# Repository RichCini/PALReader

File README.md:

This is a small archive of PAL reading code and schematics from Chuck Guzis as discussed on the VCF Forums.

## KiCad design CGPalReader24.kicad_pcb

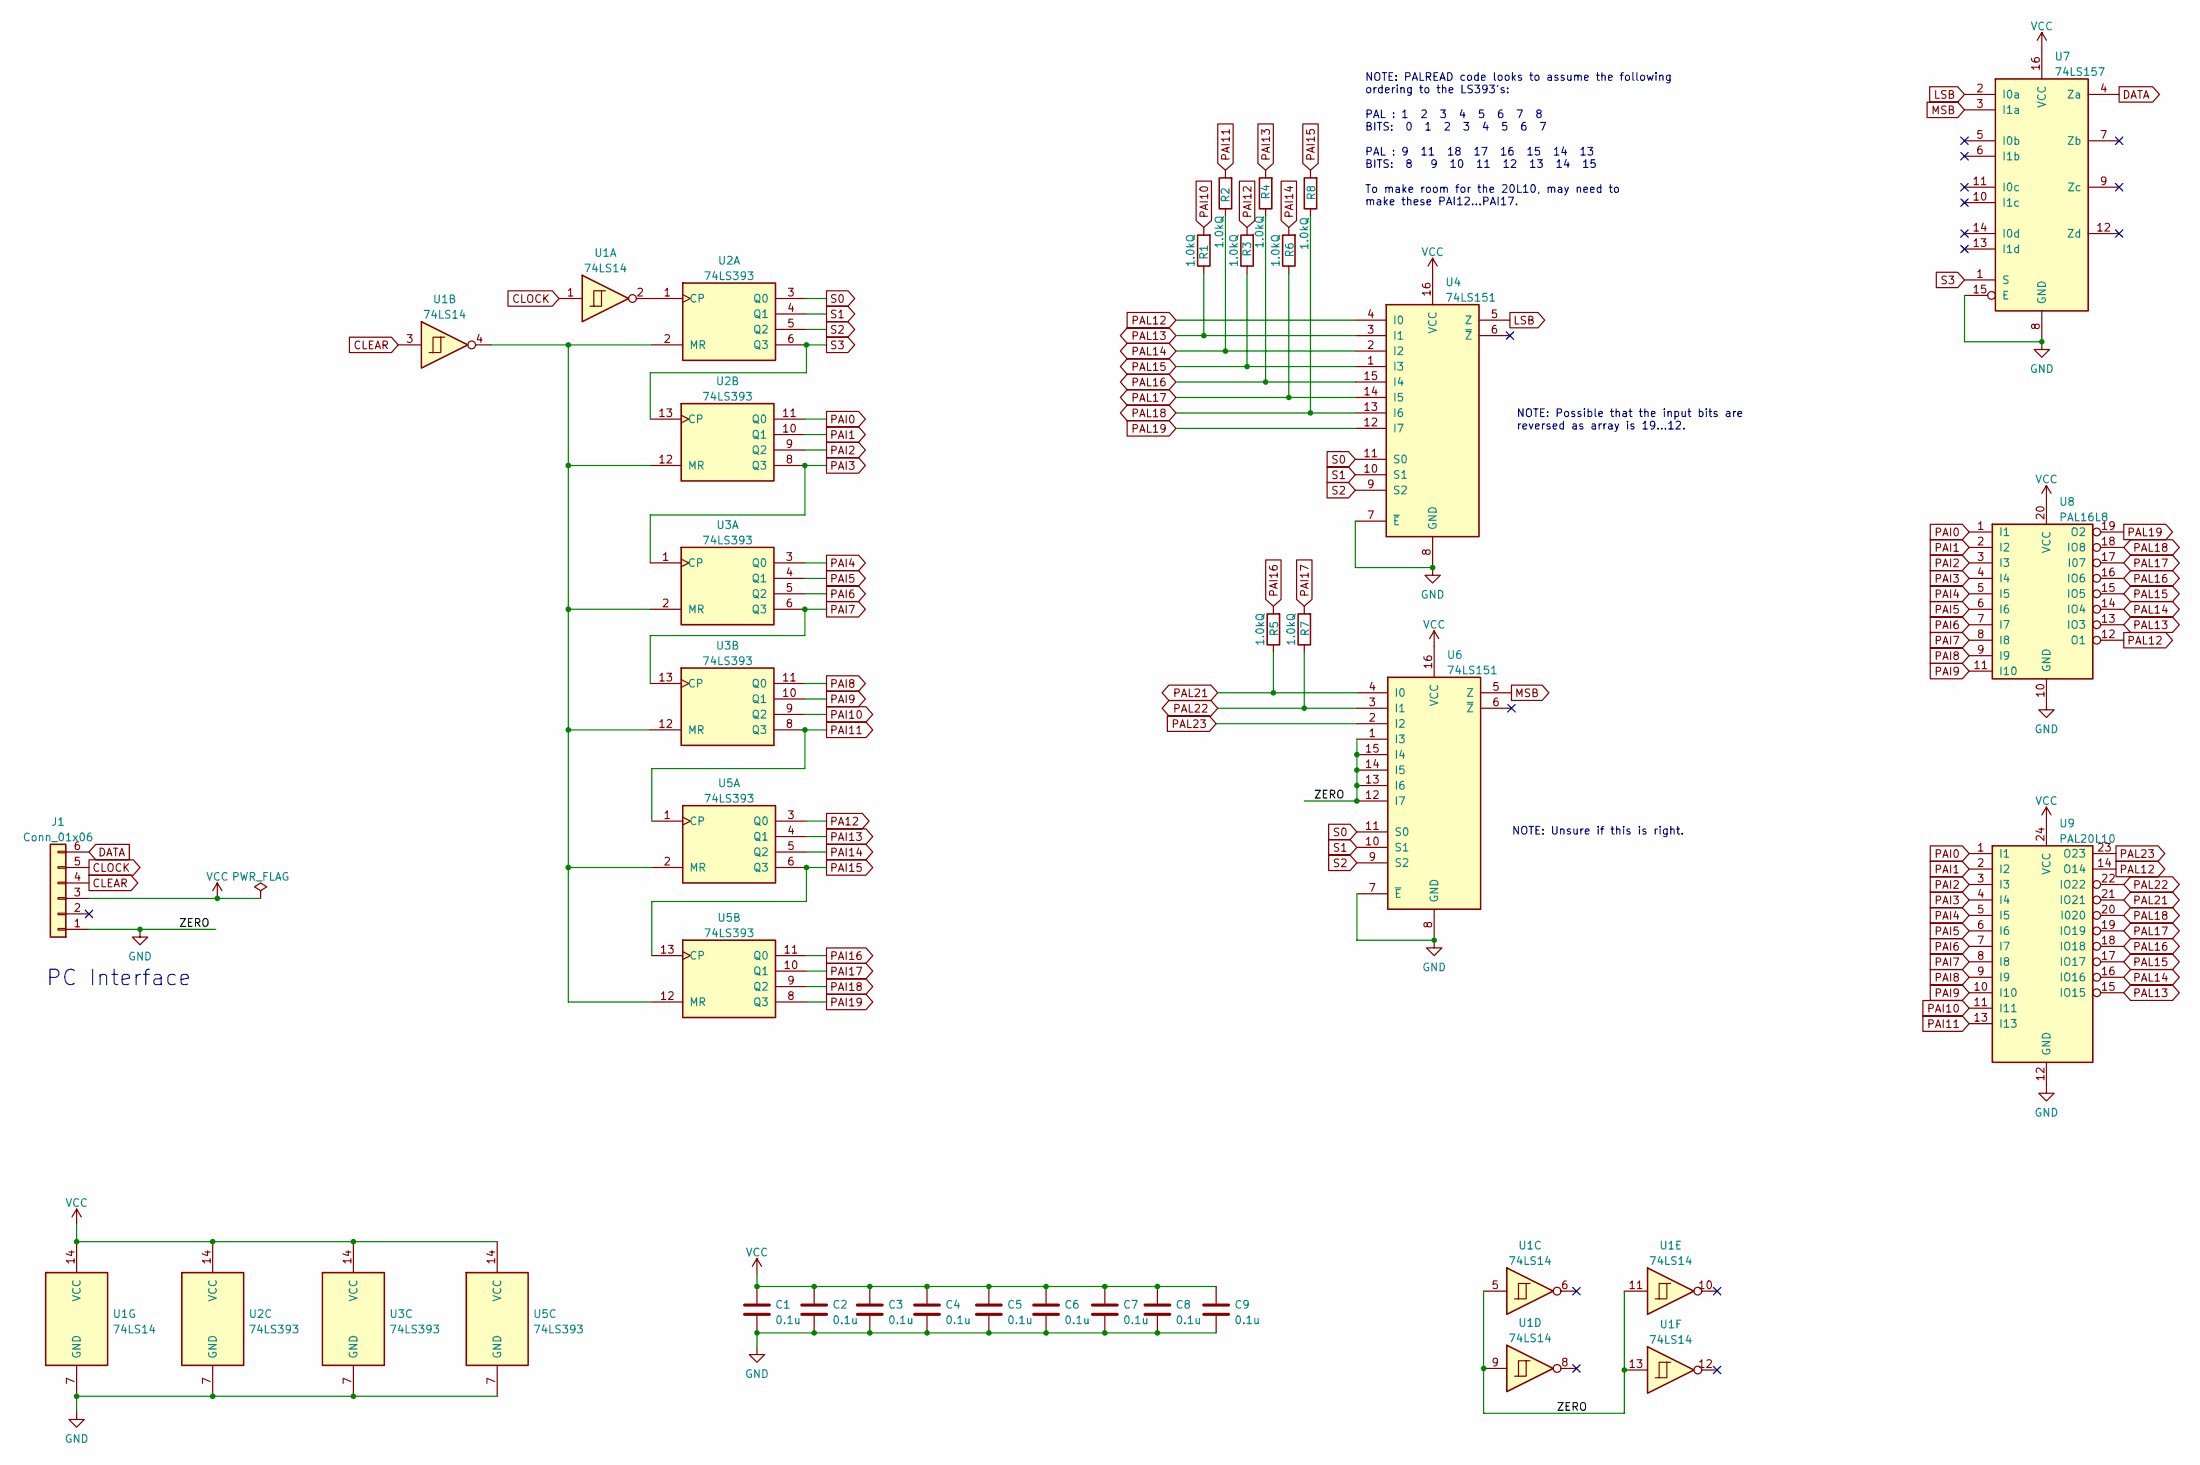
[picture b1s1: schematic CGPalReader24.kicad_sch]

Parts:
C1, C2, C3, C4, C5, C6, C7, C8, C9: 0.1u; C_Disc_D4.3mm_W1.9mm_P5.00mm
J1: Conn_01x06; PinHeader_1x06_P2.54mm_Vertical
R1, R2, R3, R4, R5, R6, R7, R8: 1.0kQ; R_Axial_DIN0207_L6.3mm_D2.5mm_P7.62mm_Horizontal
U1: 74LS14; DIP-14_W7.62mm_Socket_LongPads
U2, U3, U5: 74LS393; DIP-14_W7.62mm_Socket_LongPads
U4, U6: 74LS151; DIP-16_W7.62mm_Socket_LongPads
U7: 74LS157; DIP-16_W7.62mm_Socket_LongPads
U8: PAL16L8; DIP-20_W7.62mm_Socket_LongPads
U9: PAL20L10; DIP-24_W7.62mm_Socket_LongPads

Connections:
CLEAR: J1.4, U1.3
CLOCK: J1.5, U1.1
DATA: J1.6, U7.4 (Za)
GND: C1.2, C2.2, C3.2, C4.2, C5.2, C6.2, C7.2, C8.2, C9.2, J1.1, U1.5, U1.7 (GND), U1.9, U1.11, U1.13, U2.7 (GND), U3.7 (GND), U4.7 (~E), U4.8 (GND), U5.7 (GND), U6.1 (I3), U6.7 (~E), U6.8 (GND), U6.12 (I7), U6.13 (I6), U6.14 (I5), U6.15 (I4), U7.8 (GND), U7.15 (E), U8.10 (GND), U9.12 (GND)
LSB: U4.5 (Z), U7.2 (I0a)
MSB: U6.5 (Z), U7.3 (I1a)
unnamed: U1.2, U2.1 (CP)
unnamed: U1.4, U2.2 (MR), U2.12 (MR), U3.2 (MR), U3.12 (MR), U5.2 (MR), U5.12 (MR)
PA12: U5.3 (Q0)
PAI0: U2.11 (Q0), U8.1 (I1), U9.1 (I1)
PAI1: U2.10 (Q1), U8.2 (I2), U9.2 (I2)
PAI2: U2.9 (Q2), U8.3 (I3), U9.3 (I3)
PAI3: U2.8 (Q3), U3.1 (CP), U8.4 (I4), U9.4 (I4)
PAI4: U3.3 (Q0), U8.5 (I5), U9.5 (I5)
PAI5: U3.4 (Q1), U8.6 (I6), U9.6 (I6)
PAI6: U3.5 (Q2), U8.7 (I7), U9.7 (I7)
PAI7: U3.6 (Q3), U3.13 (CP), U8.8 (I8), U9.8 (I8)
PAI8: U3.11 (Q0), U8.9 (I9), U9.9 (I9)
PAI9: U3.10 (Q1), U8.11 (I10), U9.10 (I10)
PAI10: R1.2, U3.9 (Q2), U9.11 (I11)
PAI11: R2.2, U3.8 (Q3), U5.1 (CP), U9.13 (I13)
PAI12: R3.2
PAI13: R4.2, U5.4 (Q1)
PAI14: R6.2, U5.5 (Q2)
PAI15: R8.2, U5.6 (Q3), U5.13 (CP)
PAI16: R5.2, U5.11 (Q0)
PAI17: R7.2, U5.10 (Q1)
PAI18: U5.9 (Q2)
PAI19: U5.8 (Q3)
PAL12: U4.4 (I0), U8.12 (O1), U9.14 (O14)
PAL13: R1.1, U4.3 (I1), U8.13 (IO3), U9.15 (IO15)
PAL14: R2.1, U4.2 (I2), U8.14 (IO4), U9.16 (IO16)
PAL15: R3.1, U4.1 (I3), U8.15 (IO5), U9.17 (IO17)
PAL16: R4.1, U4.15 (I4), U8.16 (IO6), U9.18 (IO18)
PAL17: R6.1, U4.14 (I5), U8.17 (I07), U9.19 (IO19)
PAL18: R8.1, U4.13 (I6), U8.18 (IO8), U9.20 (I020)
PAL19: U4.12 (I7), U8.19 (O2)
PAL21: R5.1, U6.4 (I0), U9.21 (IO21)
PAL22: R7.1, U6.3 (I1), U9.22 (IO22)
PAL23: U6.2 (I2), U9.23 (O23)
S0: U2.3 (Q0), U4.11 (S0), U6.11 (S0)
S1: U2.4 (Q1), U4.10 (S1), U6.10 (S1)
S2: U2.5 (Q2), U4.9 (S2), U6.9 (S2)
S3: U2.6 (Q3), U2.13 (CP), U7.1 (S)
VCC: C1.1, C2.1, C3.1, C4.1, C5.1, C6.1, C7.1, C8.1, C9.1, J1.3, U1.14 (VCC), U2.14 (VCC), U3.14 (VCC), U4.16 (VCC), U5.14 (VCC), U6.16 (VCC), U7.16 (VCC), U8.20 (VCC), U9.24 (VCC)

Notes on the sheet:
NOTE: Possible that the input bits are reversed as array is 19...12.
PC Interface
NOTE: PALREAD code looks to assume the following ordering to the LS393's: PAL : 1 2 3 4 5 6 7 8 BITS: 0 1 2 3 4 5 6 7 PAL : 9 11 18 17 16 15 14 13 BITS: 8 9 10 11 12 13 14 15 To make room for the 20L10, may need to make these PAI12...PAI17.
NOTE: Unsure if this is right.

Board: 2 copper layers, 27 parts (0 on the bottom side), 41 nets, no tracks yet.

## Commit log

2023-05-19 Add files via upload
    Changed input pin ordering.

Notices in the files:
CGPalReader24.kicad_pcb:
(c) 2023
